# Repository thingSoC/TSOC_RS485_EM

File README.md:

# TSOC_RS485_EM
**TSOC_RS485_EM** is a ATMEGA328 based board with integrated RS485 driver, an Embedded Module for thingSoC.

The **TSOC_RS485_EM** connects any thingSoC or Mikrobus module to an RS485 compatible slave interface,
including a variety of analog sensors, such as Temperature, Wind, Pressure, Air Quality, and much more.
The **TSOC_RS485_EM** can be configured as either a thingSoC master module (female connectors), or a thingSoC slave module (male connectors),
which is implemented as an assembly/build time option.
 
---------------------------------------

[TSOC_RS485_EM](https://github.com/thingSoC/TSOC_RS485_EM/)

* [thingSoC Compliant Module](http://www.thingsoc.com)
* [Mikrobus Compatible Module](http://www.mikroe.com/mikrobus/) 
* [Modbus](http://www.modbus.org/specs.php) Compliant Slave Interface
* [5 Volt](https://en.wikipedia.org/wiki/Modbus) Nominal Power Input with ESD and OV/OC protections
* Supports Analog  Inputs  (ADC) 
* Supports Digital Outputs (GPIO)
* Supports Digital Inputs  (GPIO)
* Supports Remote I2C Interface
* Supports Remote UART Interface
* Supports Remote SPI Interface

## Protocols

* DMX512, RDM512
* Modbus
* Vending Machine Bus

---------------------------------------
## Example Applications

[TSOC_RS485_EM Example Wiring](https://github.com/thingSoC/TSOC_RS485_EM/)

* [Modbus Weather Sensor](http://www.mikroe.com/click/weather/) BOSCH BME280 Temp, Humidity, Air Pressure
* [Modbus Methane Sensor](http://www.mikroe.com/click/methane/) MQ-4 Sensor for Methane (CH4) 
* [Modbus Air Quality Sensor](http://www.mikroe.com/click/air-quality/) MQ-135 Sensor for Harmful Gasses
* [Modbus Lightning Sensor](http://www.mikroe.com/click/thunder/) AS3935 Lighting Strike Detector
* [Modbus Controlled Relay](http://www.mikroe.com/click/relay/) G6D1AASI Power Relay Control Module

---------------------------------------
## 3D Model (Sketchup)

---------------------------------------
## Project Status

* 02/18/2016 : Revision 4.0 Release for PCB fab
* 03/07/2016 : First Prototypes, board bringup is good
* 03/14/2016 : Revision 5.0 Released for PCB
* 04/06/2016 : Revision 6.0 Released for PCB

## Revision 6.0 Notes: ##

* Pinout Changes, D5/D8/D9 added as a second serial choice
* Disconnect jumpers added to all shared pins
* A7 used as AREF calibration input
* A6 used as VCC monitor input
* Both 3.5mm and 2.54mm connector patterns added

---------------------------------------

## Documentation Index <a name="documentation_index"/>

[TSOC_RS485_EM Quick Start Guide](https://github.com/thingSoC/TSOC_RS485_EM/blob/master/TSOC_RS485_EM/docs/QuickStart.md)

[TSOC_RS485_EM User Guide](https://github.com/thingSoC/TSOC_RS485_EM/blob/master/TSOC_RS485_EM/docs/UserGuide.md)

[TSOC_RS485_EM Theory of Operation](https://github.com/thingSoC/TSOC_RS485_EM/blob/master/TSOC_RS485_EM/docs/TheoryOfOperation.md)

[thingSoC Organization Website](http://thingSoC.github.io)

[thingSoC FAQ - Frequently Asked Questions](http://thingsoc.github.io/support/faq.html)

---------------------------------------

[  
*thingSoC*](http://thingsoc.github.io)

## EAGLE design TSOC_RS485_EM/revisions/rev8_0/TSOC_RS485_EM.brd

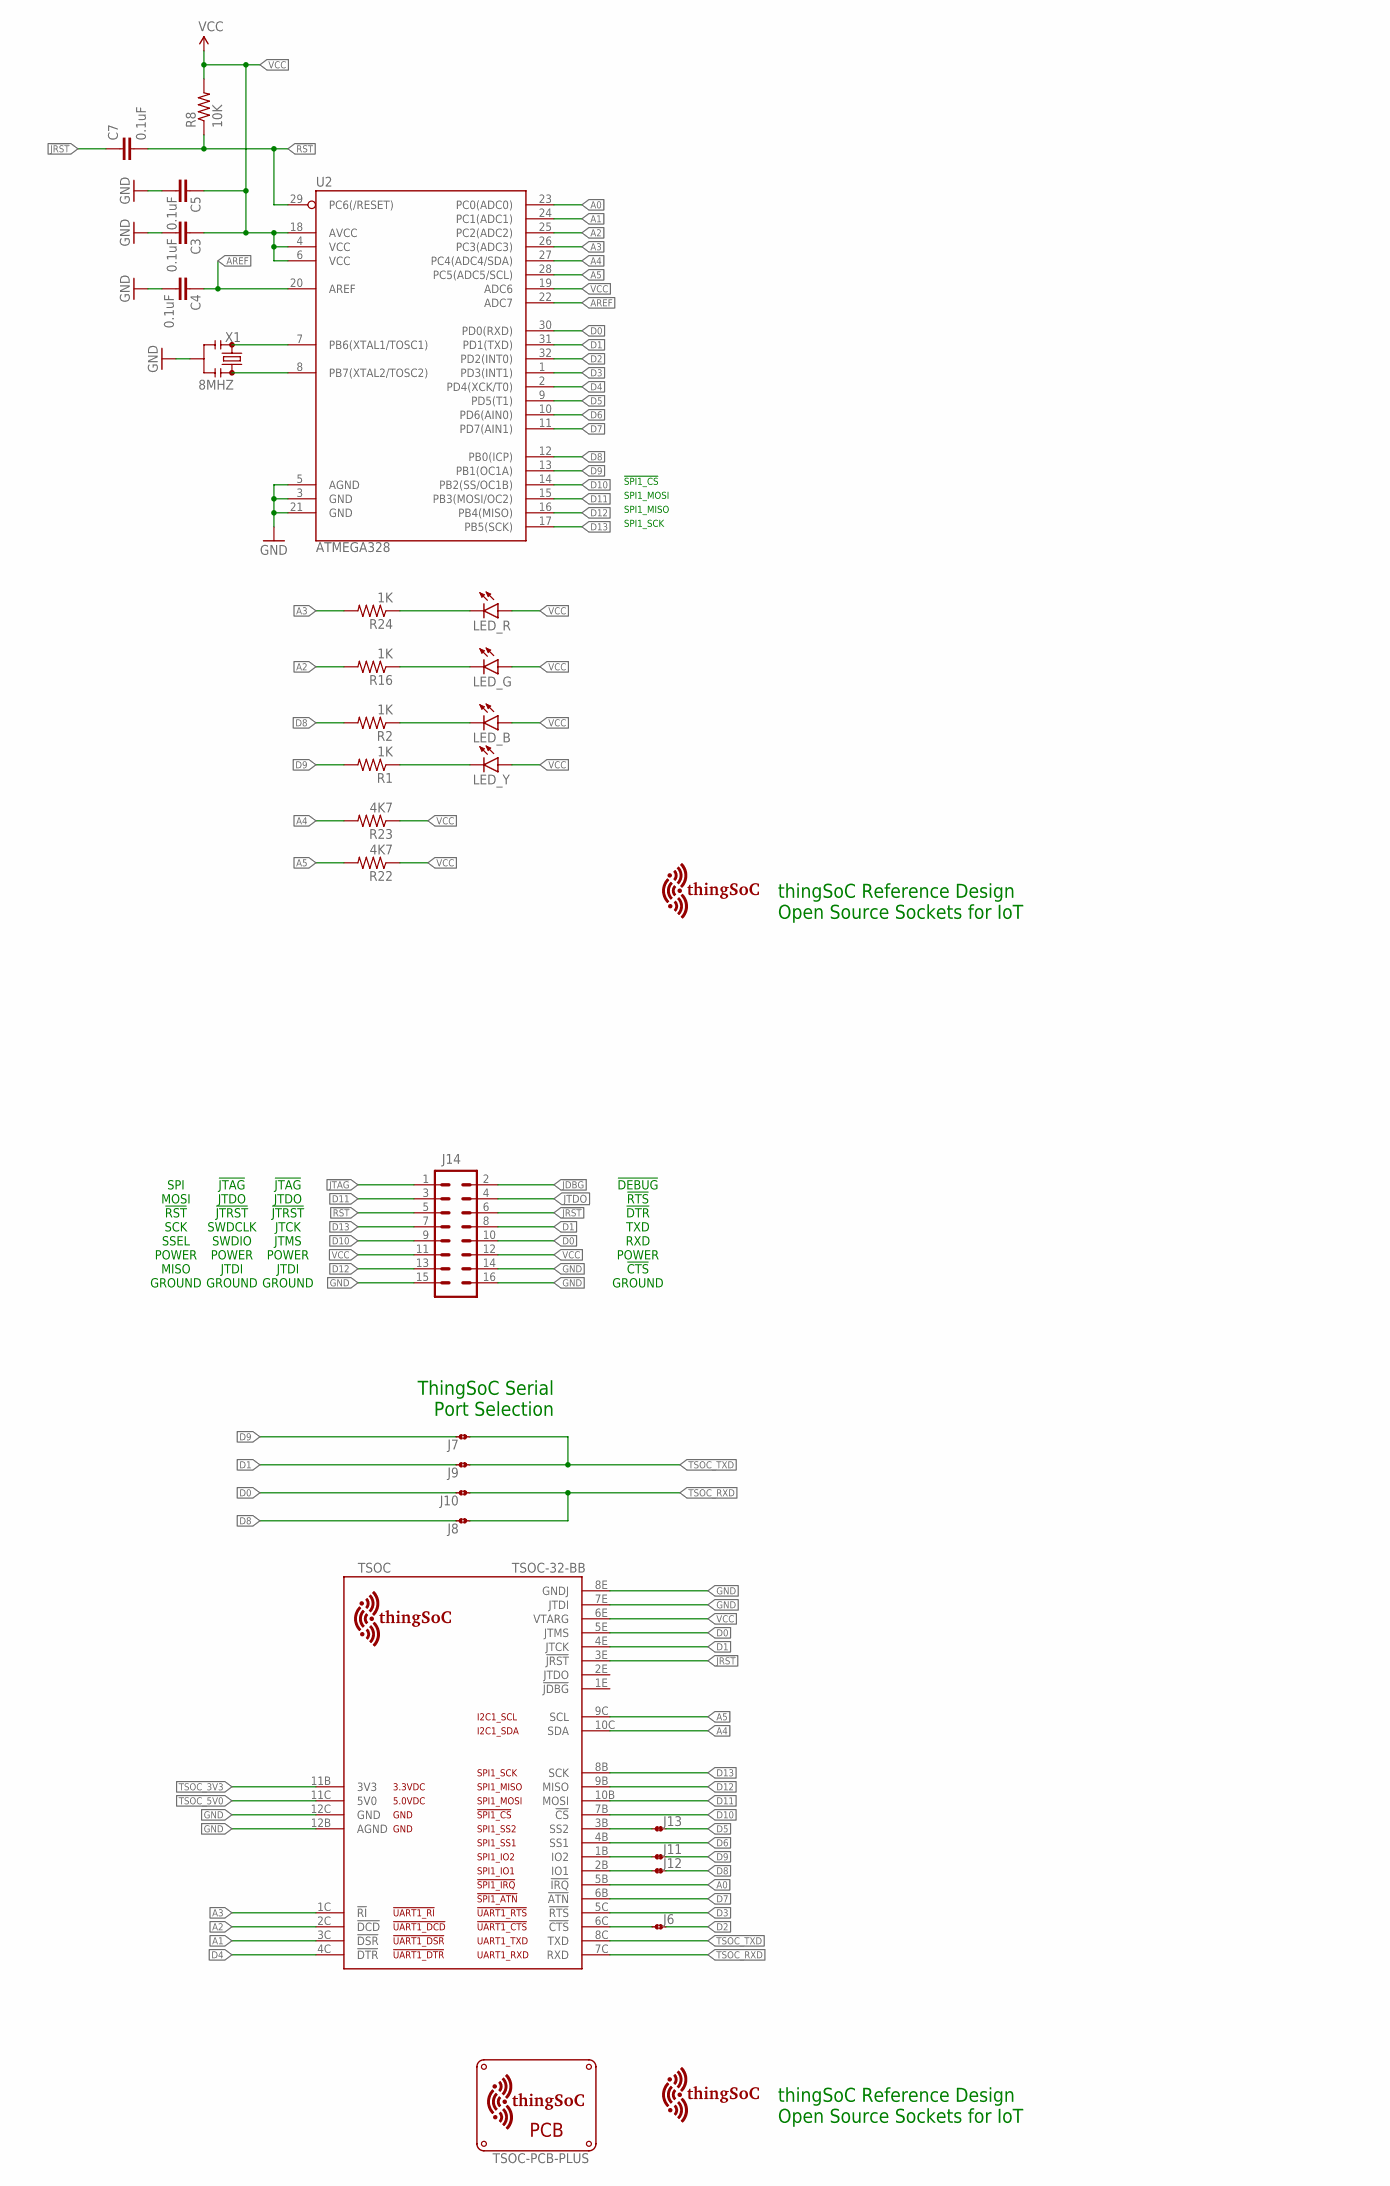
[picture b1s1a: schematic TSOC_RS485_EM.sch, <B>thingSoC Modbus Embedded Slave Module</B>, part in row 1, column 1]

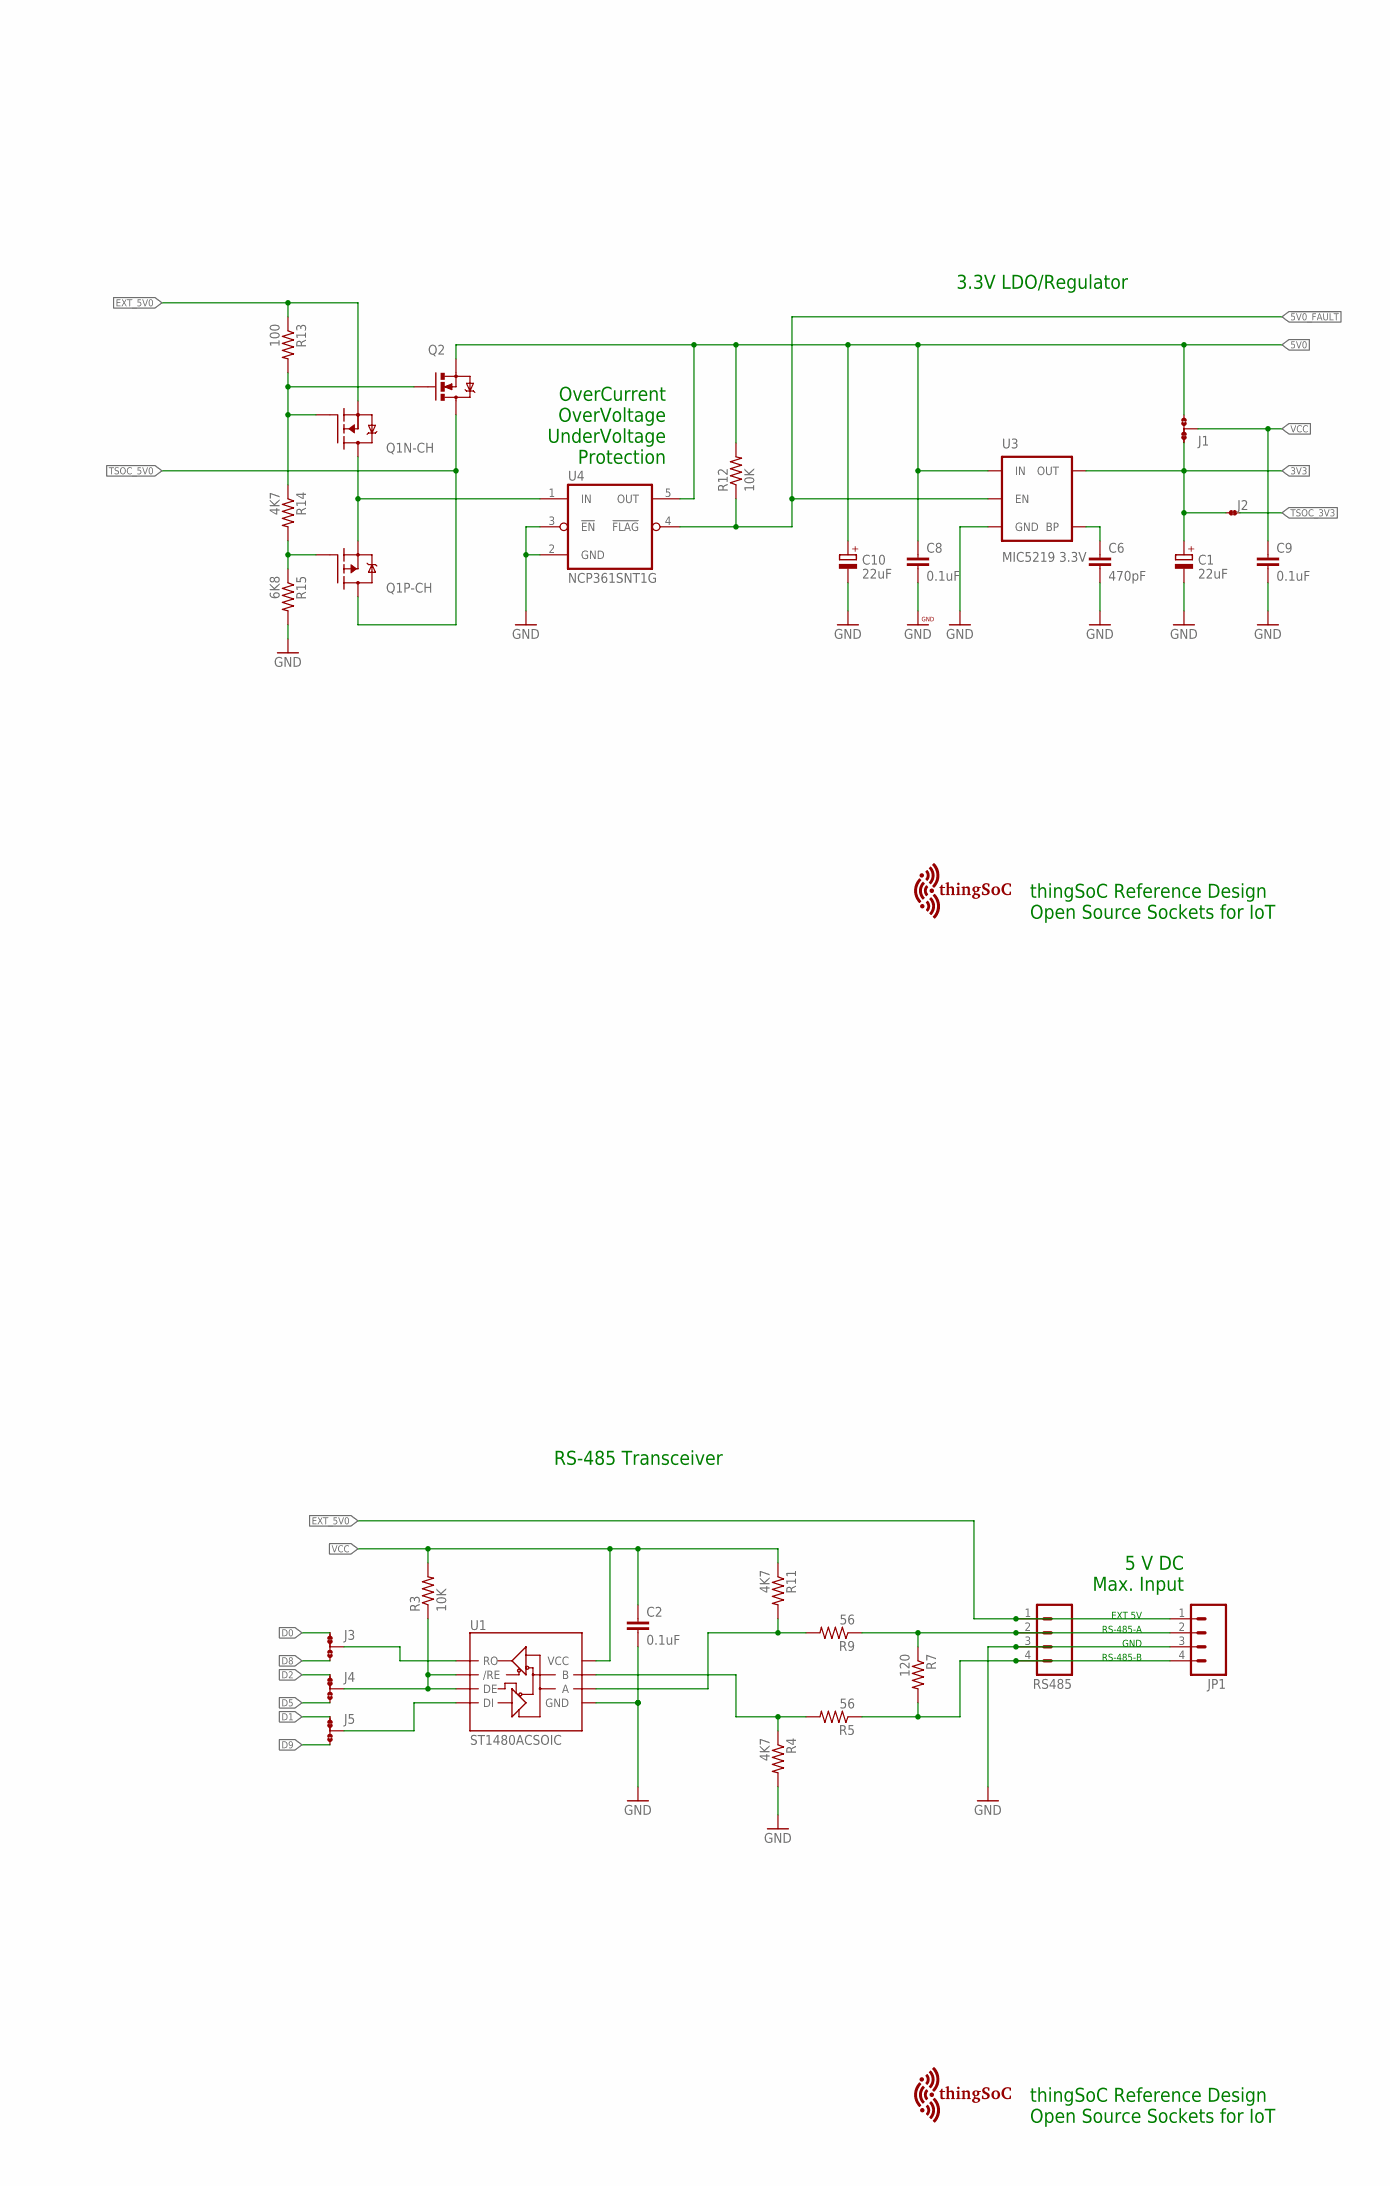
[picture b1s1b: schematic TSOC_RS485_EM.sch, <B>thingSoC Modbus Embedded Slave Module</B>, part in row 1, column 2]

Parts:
C1, C10: 22uF; SMC_B
C2, C3, C4, C5, C7, C8, C9: 0.1uF; EIA-0402
C6: 470pF; EIA-0402
J1, J3, J4, J5: JMP-3-1_2
J2, J11, J12, J13: JMP-2-NC
J6, J7, J8, J9, J10: JMP-2-NO
J14: M08X2; 2X8
JP1: M04PTH; 1X04
LED_B: LED0603; LED-0603
LED_G: LED0603; LED-0603
LED_R: LED0603; LED-0603
LED_Y: LED0603; LED-0603
Q1: FDC6420C; SOT95P280X110-6N
Q2: MOSFET-NCHANNELAO3404A; SOT23-3
R1, R2, R16, R24: 1K; EIA-0402-MIN
R3, R8, R12: 10K; EIA-0402-MIN
R4, R11, R14, R22, R23: 4K7; EIA-0402-MIN
R5, R9: 56; EIA-0402-MIN
R7: 120; EIA-0402-MIN
R13: 100; EIA-0402-MIN
R15: 6K8; EIA-0402-MIN
RS485: M04SCREW; SCREWTERMINAL-3.5MM-4
TSOC: TSOC-32-BB; TSOC-BB-S32
U1: ST1480ACSOIC; SO08
U2: ATMEGA328; TQFP32-08
U3: MIC5219 3.3V; SOT23-5
U4: NCP361SNT1G; SOP95P275X110-5N
U$3: TSOC-PCB-PLUS; TSOC-BB-BRD-PLUS
U$5, U$6, U$7, U$8: TSOC-LOGO-SMALL; TSOC-LOGO-SML
X1: 8MHZ; RESONATOR-SMD

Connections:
3V3: C1.+, J1.1, J2.1, U3.5 (OUT)
5V0: C8.1, C10.+, J1.3, Q2.2 (S), R12.2, U3.1 (IN), U4.5 (OUT)
!5V0_FAULT: R12.1, U3.3 (EN), U4.4 (!FLAG)
!JDBG: J14.2
!JRST: C7.1, J14.6, TSOC.3E (!JRST)
!JTAG: J14.1
!RST: C7.2, J14.5, R8.1, U2.29 (PC6(/RESET))
A: R9.2, R11.2, U1.6 (A)
A0: TSOC.5B (!IRQ), U2.23 (PC0(ADC0))
A1: TSOC.3C (!DSR), U2.24 (PC1(ADC1))
A2: R16.2, TSOC.2C (!DCD), U2.25 (PC2(ADC2))
A3: R24.2, TSOC.1C (!RI), U2.26 (PC3(ADC3))
A4: R23.2, TSOC.10C (SDA), U2.27 (PC4(ADC4/SDA))
A5: R22.2, TSOC.9C (SCL), U2.28 (PC5(ADC5/SCL))
AO: JP1.2, R7.1, R9.1, RS485.2
AREF: C4.2, U2.20 (AREF), U2.22 (ADC7)
B: R4.1, R5.2, U1.7 (B)
BO: JP1.4, R5.1, R7.2, RS485.4
BYPASS1: C6.1, U3.4 (BP)
D0: J3.1, J10.2, J14.10, TSOC.5E (JTMS), U2.30 (PD0(RXD))
D1: J5.1, J9.2, J14.8, TSOC.4E (JTCK), U2.31 (PD1(TXD))
D2: J4.1, J6.2, U2.32 (PD2(INT0))
D3: TSOC.5C (!RTS), U2.1 (PD3(INT1))
D4: TSOC.4C (!DTR), U2.2 (PD4(XCK/T0))
D5: J4.3, J13.2, U2.9 (PD5(T1))
D6: TSOC.4B (SS1), U2.10 (PD6(AIN0))
D7: TSOC.6B (!ATN), U2.11 (PD7(AIN1))
D8: J3.3, J8.2, J12.2, R2.2, U2.12 (PB0(ICP))
D9: J5.3, J7.2, J11.2, R1.2, U2.13 (PB1(OC1A))
D10: J14.9, TSOC.7B (!CS), U2.14 (PB2(SS/OC1B))
D11: J14.3, TSOC.10B (MOSI), U2.15 (PB3(MOSI/OC2))
D12: J14.13, TSOC.9B (MISO), U2.16 (PB4(MISO))
D13: J14.7, TSOC.8B (SCK), U2.17 (PB5(SCK))
DE: J4.2, R3.1, U1.2 (/RE), U1.3 (DE)
DI: J5.2, U1.4 (DI)
EXT_5V0: JP1.1, Q1.5 (S), R13.1, RS485.1
GND: C1.-, C2.2, C3.1, C4.1, C5.1, C6.2, C8.2, C9.2, C10.-, J14.14, J14.15, J14.16, JP1.3, R4.2, R15.2, RS485.3, TSOC.7E (JTDI), TSOC.8E (GNDJ), TSOC.12B (AGND), TSOC.12C (GND), U1.5 (GND), U2.3 (GND), U2.5 (AGND), U2.21 (GND), U3.2 (GND), U4.2 (GND), U4.3 (!EN), X1.2
JTDO: J14.4
LEDB: LED_B.C, R2.1
LEDG: LED_G.C, R16.1
LEDR: LED_R.C, R24.1
LEDY: LED_Y.C, R1.1
unnamed: J13.1, TSOC.3B (SS2)
NGATE: Q1.1 (G), Q2.1 (G), R13.2, R14.1
PGATE: Q1.3 (G), R14.2, R15.1
RXD: J3.2, U1.1 (RO)
TSOC_3V3: J2.2, TSOC.11B (3V3)
TSOC_5V0: Q1.4 (D), Q2.3 (D), TSOC.11C (5V0)
TSOC_CTS: J6.1, TSOC.6C (!CTS)
TSOC_D8: J12.1, TSOC.2B (IO1)
TSOC_D9: J11.1, TSOC.1B (IO2)
TSOC_RXD: J8.1, J10.1, TSOC.7C (RXD)
TSOC_TXD: J7.1, J9.1, TSOC.8C (TXD)
VCC: C2.1, C3.2, C5.2, C9.1, J1.2, J14.11, J14.12, LED_B.A, LED_G.A, LED_R.A, LED_Y.A, R3.2, R8.2, R11.1, R22.1, R23.1, TSOC.6E (VTARG), U1.8 (VCC), U2.4 (VCC), U2.6 (VCC), U2.18 (AVCC), U2.19 (ADC6)
VIN: Q1.2 (S), Q1.6 (D), U4.1 (IN)
XIN: U2.7 (PB6(XTAL1/TOSC1)), X1.3
XOUT: U2.8 (PB7(XTAL2/TOSC2)), X1.1

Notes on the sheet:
SPI1_SCK
SPI1_MISO
SPI1_MOSI
!SPI1_CS
5 V DC Max. Input
OverCurrent OverVoltage UnderVoltage Protection
3.3V LDO/Regulator
RS-485 Transceiver
EXT 5V
GND
RS-485-A
RS-485-B
ThingSoC Serial Port Selection
thingSoC Reference Design Open Source Sockets for IoT
!DEBUG
!RTS
!CTS
!DTR
TXD
RXD
POWER
GROUND
JTDI
JTDO
!JTRST
JTCK
JTMS
!JTAG
SWDCLK
SWDIO
SCK
SSEL
SPI
MOSI
!RST
MISO

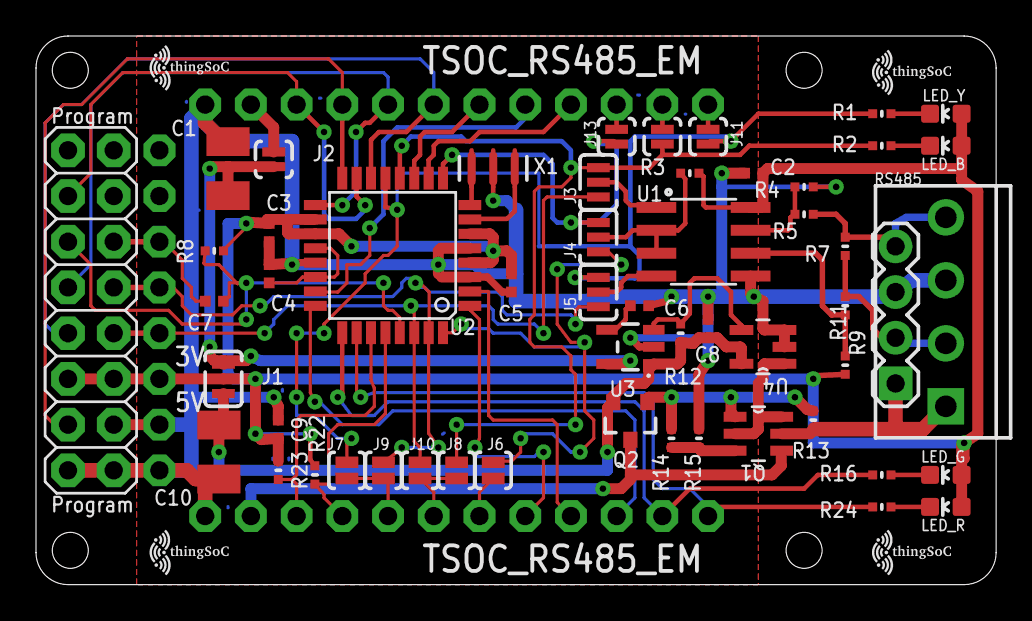
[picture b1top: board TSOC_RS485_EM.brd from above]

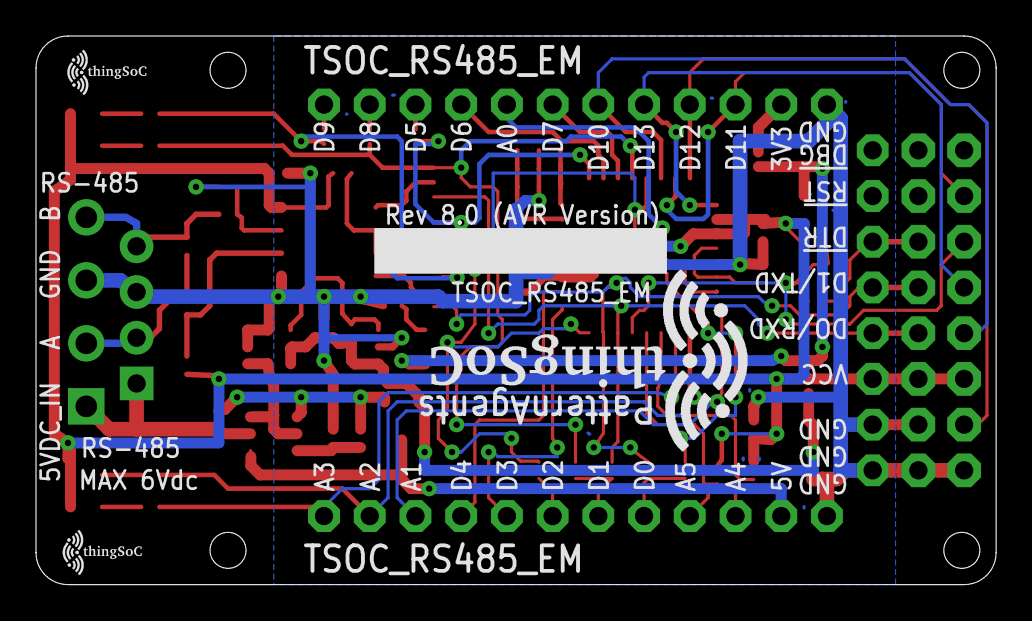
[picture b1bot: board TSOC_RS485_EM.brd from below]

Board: 2 copper layers, 53.3 x 30.5 mm, 63 parts (3 on the bottom side), 54 nets.

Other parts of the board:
U$1, U$4: TSOC-LOGO-SMALL; TSOC-LOGO-SML
U$100: TSOC-LOGO-LRG

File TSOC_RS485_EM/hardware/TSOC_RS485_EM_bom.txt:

Partlist exported from /home/moxon/github/TSOC_RS485_EM/TSOC_RS485_EM/TSOC_RS485_EM.sch at 4/6/16 2:10 PM

Qty Value                  Device                 Package               Parts                      Description                                            
5                          JMP-2-NO               JMP-2-NO              J6, J7, J8, J9, J10        Two Terminal Jumper - Normally Open                    
4                          LED0603                LED-0603              LED_B, LED_G, LED_R, LED_Y LEDs                                                   
1                          M04PTH                 1X04                  JP1                        Header 4                                               
1                          M04SCREW               SCREWTERMINAL-3.5MM-4 RS485                      Header 4                                               
7   0.1uF                  CAP0402-CAP            0402-CAP              C2, C3, C4, C5, C7, C8, C9 Capacitor                                              
1   100                    RESISTOR0402           0402-RES              R13                        Resistor                                               
3   10K                    RESISTOR0402           0402-RES              R3, R8, R12                Resistor                                               
1   120                    RESISTOR0402           0402-RES              R7                         Resistor                                               
4   1K                     RESISTOR0402           0402-RES              R1, R2, R16, R24           Resistor                                               
2   22uF                   CPOL-EUSMCB            SMC_B                 C1, C10                    POLARIZED CAPACITOR, European symbol                   
1   470pF                  CAP0402-CAP            0402-CAP              C6                         Capacitor                                              
5   4K7                    RESISTOR0402           0402-RES              R4, R11, R14, R22, R23     Resistor                                               
2   56                     RESISTOR0402           0402-RES              R5, R9                     Resistor                                               
1   6K8                    RESISTOR0402           0402-RES              R15                        Resistor                                               
1   8MHZ                   RESONATOR8MHZ          RESONATOR-SMD         X1                         Resonator                                              
1   ATMEGA328              ATMEGA168              TQFP32-08             U2                                                                                
2   DNP                    RESISTOR0402           0402-RES              R6, R10                    Resistor                                               
1   FDC6420C               FDC6420C               SOT95P280X110-6N      Q1                         N and P Channel Power Trench MOSFETs                   
4   JMP-2-NC               JMP-2-NC               JMP-2-NC              J2, J11, J12, J13          Two Terminal Jumper - Normally Closed                  
4   JMP-3-1_2              JMP-3-1_2              JMP-3-1_2             J1, J3, J4, J5             Three Terminal Jumper - 1 & 2 Connected                
1   MIC5219 3.3V           V_REG_MIC52193.3V      SOT23-5               U3                         V_REG MIC5219                                          
1   MOSFET-NCHANNELAO3404A MOSFET-NCHANNELAO3404A SOT23-3               Q2                         Common NMOSFET Parts                                   
1   NCP361SNT1G            NCP361SNT1G            SOP95P275X110-5N      U4                         USB Positive Overvoltage Protection Controller         
1   ST1480ACSOIC           ST1480ACSOIC           SO08                  U1                         ST Microelectronics ST1480AC RS-485/RS-422 Transceiver 
1   TSOC-32-BB             TSOC-32-BB             TSOC-BB-S32           TSOC                       thingSoC Thirty-Two (32) Pin Socket                    
1   TSOC-PCB-EM-45         TSOC-PCB-EM-45         TSOC-EM-BB-45MM       U$1                        thingSoC PCB Outlines

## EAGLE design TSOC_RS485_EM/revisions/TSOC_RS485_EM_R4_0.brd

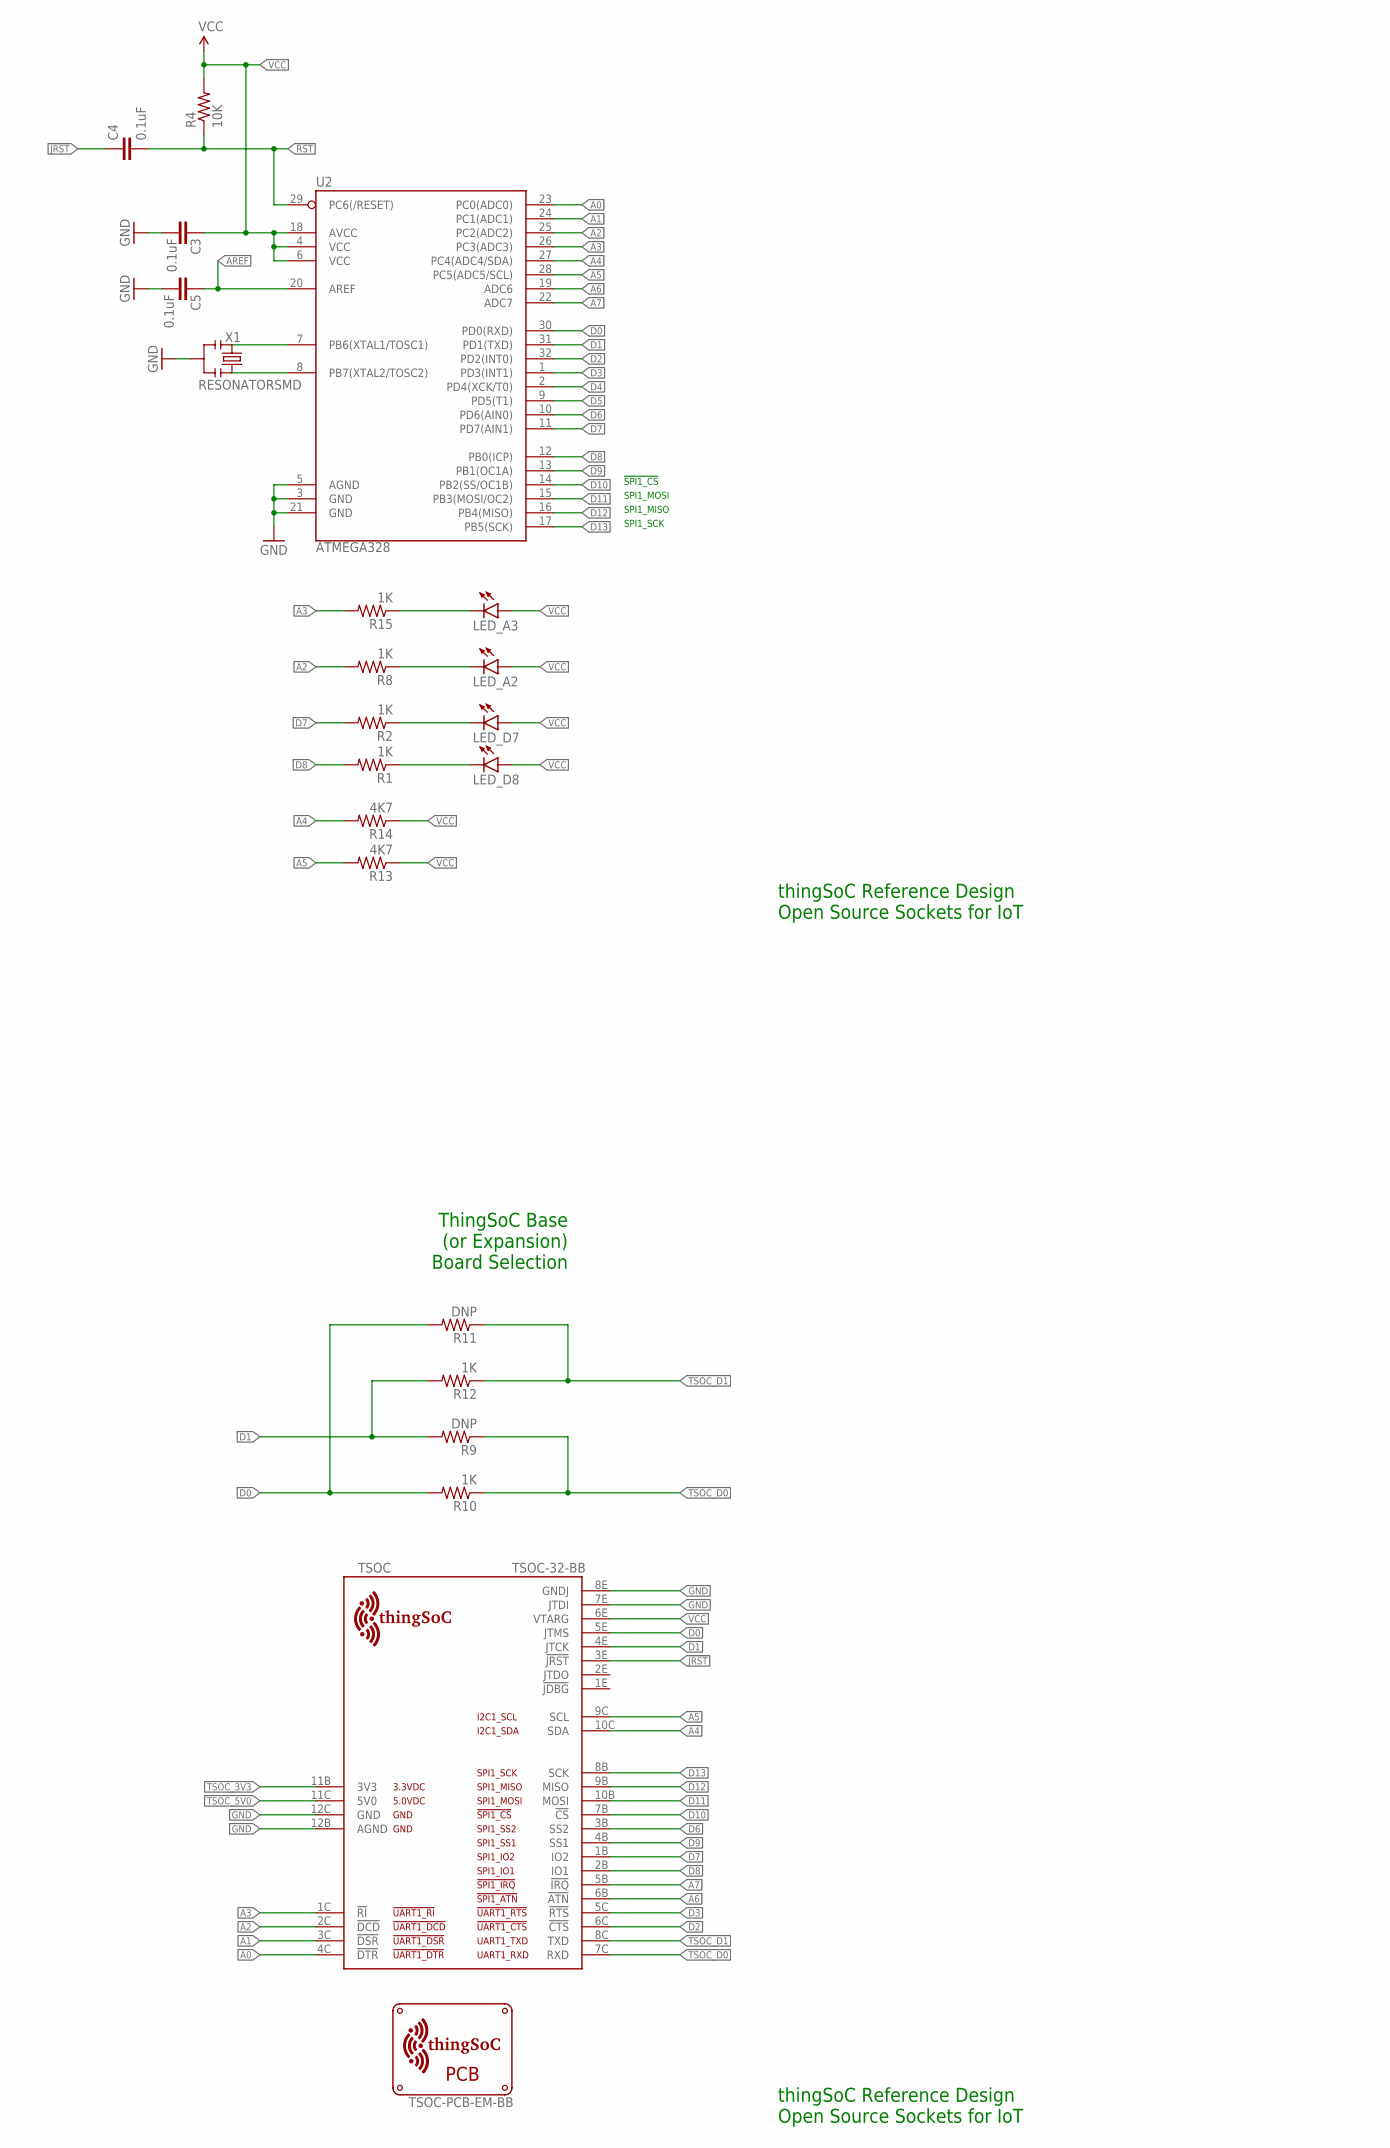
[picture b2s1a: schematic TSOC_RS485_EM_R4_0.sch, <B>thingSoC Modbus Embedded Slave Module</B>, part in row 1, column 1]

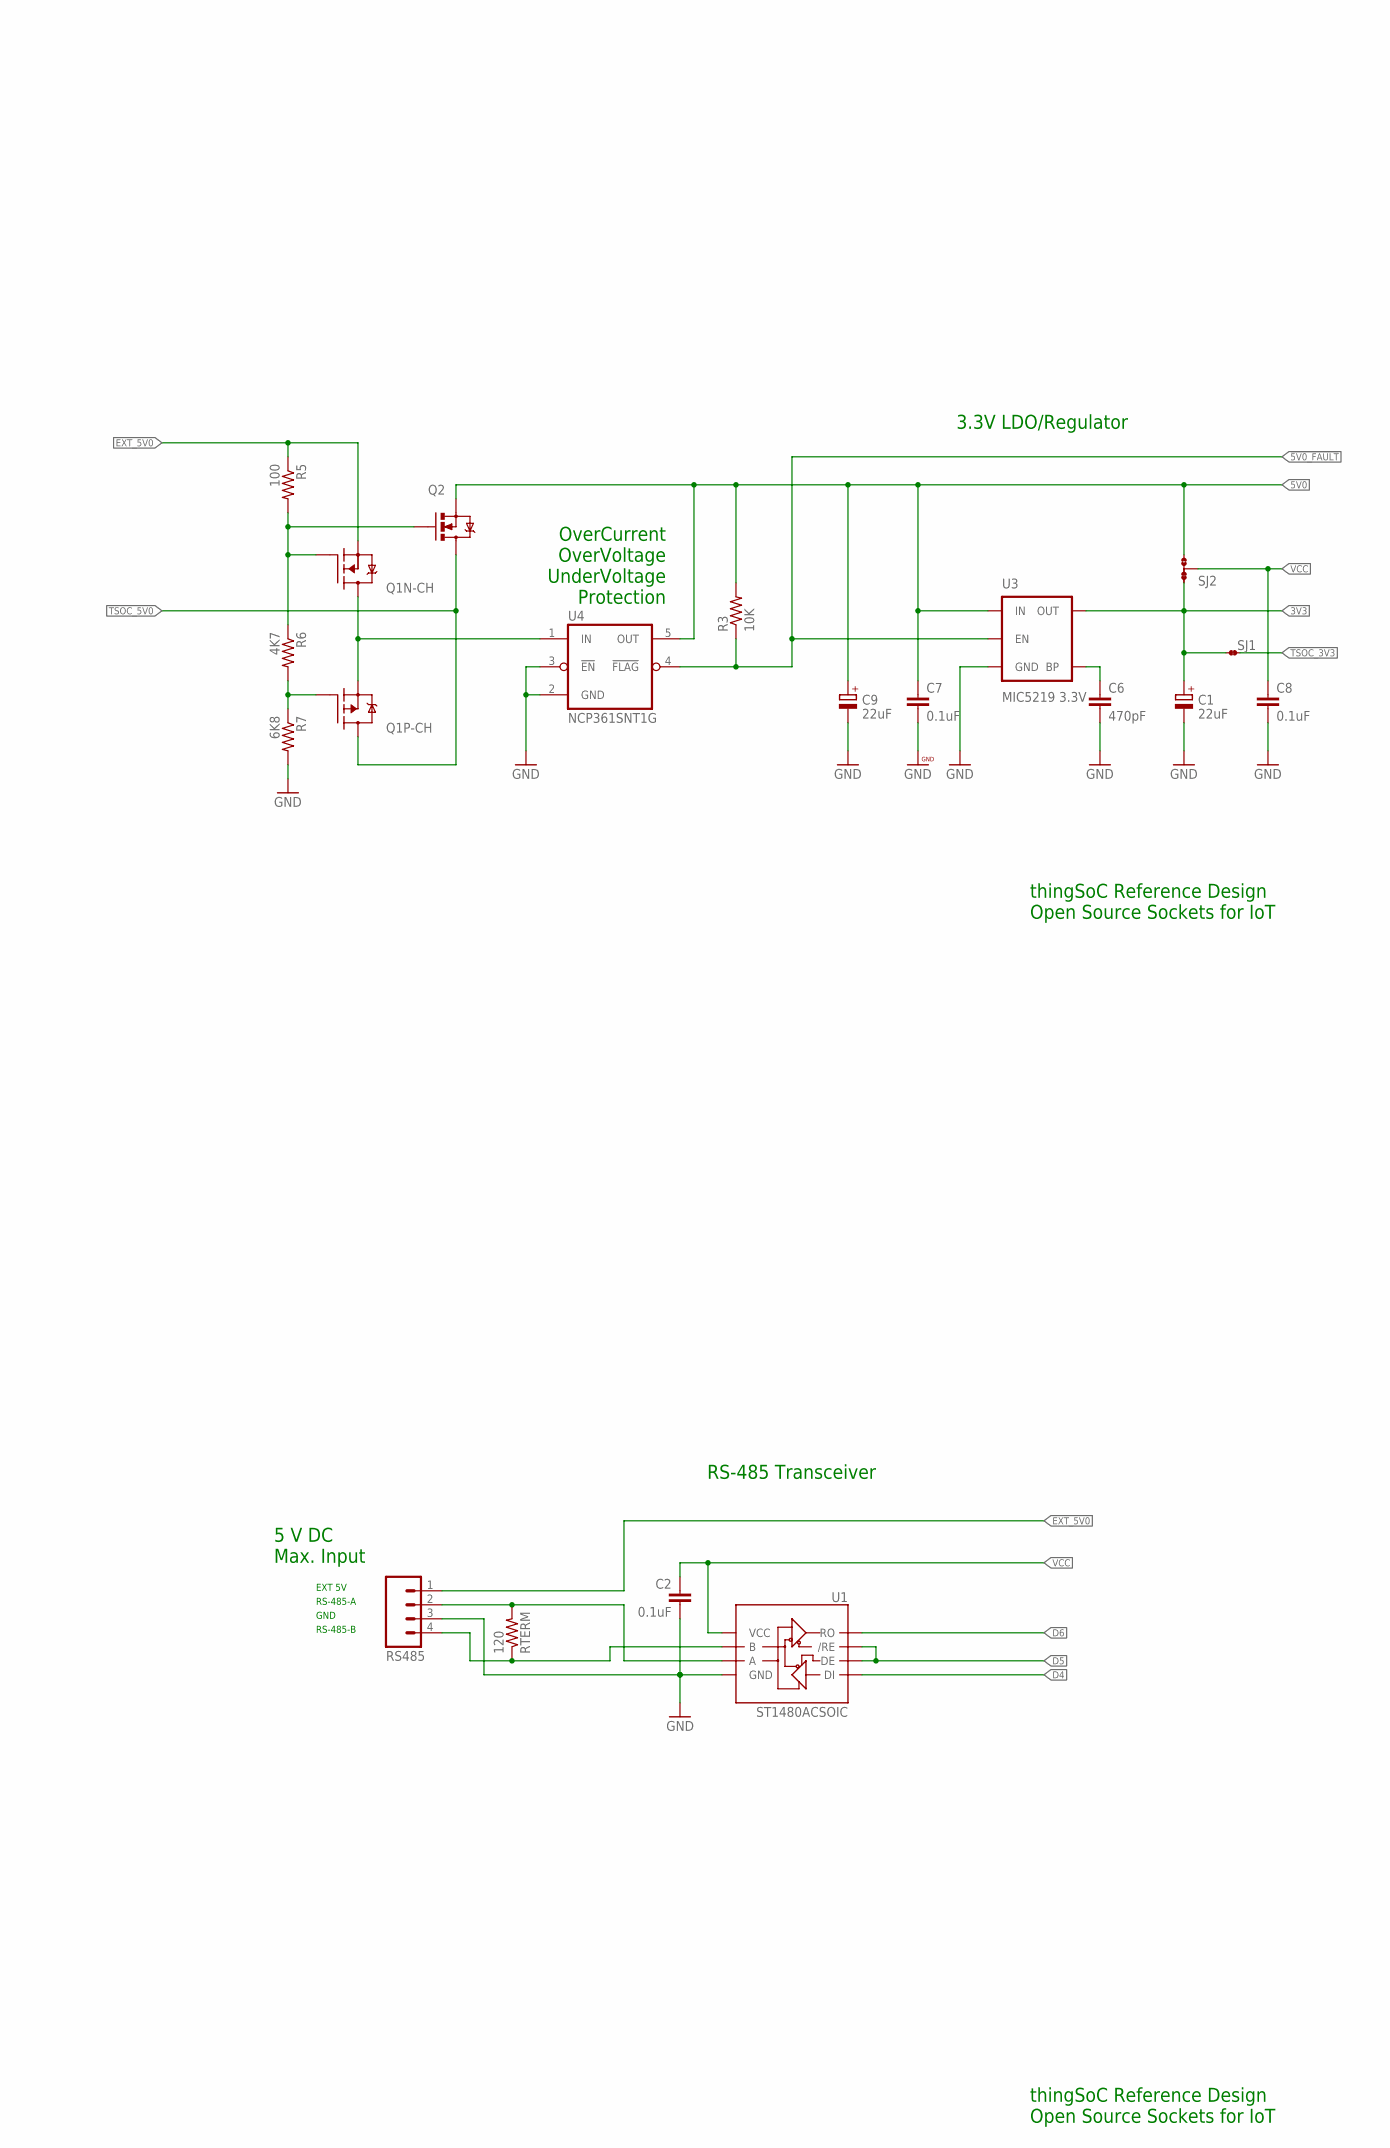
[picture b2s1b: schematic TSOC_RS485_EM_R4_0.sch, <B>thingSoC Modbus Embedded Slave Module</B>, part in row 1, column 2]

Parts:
C1, C9: 22uF; SMC_B
C2, C3, C4, C5, C7, C8: 0.1uF; 0402-CAP
C6: 470pF; 0402-CAP
LED_A2, LED_A3: LED0603; LED-0603
LED_D7, LED_D8: LED0603; LED-0603
Q1: FDC6420C; SOT95P280X110-6N
Q2: MOSFET-NCHANNELAO3404A; SOT23-3
R1, R2, R8, R10, R12, R15: 1K; 0402-RES
R3, R4: 10K; 0402-RES
R5: 100; 0402-RES
R6, R13, R14: 4K7; 0402-RES
R7: 6K8; 0402-RES
R9, R11: DNP; 0402-RES
RS485: M04SCREW; SCREWTERMINAL-3.5MM-4
RTERM: 120; 0402-RES
SJ1: JMP-2-NC
SJ2: JMP-3-1_2
TSOC: TSOC-32-BB; TSOC-BB-S32
U1: ST1480ACSOIC; SO08
U2: ATMEGA328; TQFP32-08
U3: MIC5219 3.3V; SOT23-5
U4: NCP361SNT1G; SOP95P275X110-5N
U$1: TSOC-PCB-EM-BB; TSOC-EM-BB
X1: RESONATORSMD; RESONATOR-SMD

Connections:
3V3: C1.+, SJ1.1, SJ2.1, U3.5 (OUT)
5V0: C7.1, C9.+, Q2.2 (S), R3.2, SJ2.3, U3.1 (IN), U4.5 (OUT)
!5V0_FAULT: R3.1, U3.3 (EN), U4.4 (!FLAG)
!JRST: C4.1, TSOC.3E (!JRST)
!RST: C4.2, R4.1, U2.29 (PC6(/RESET))
A: RS485.4, RTERM.1, U1.7 (B)
A0: TSOC.4C (!DTR), U2.23 (PC0(ADC0))
A1: TSOC.3C (!DSR), U2.24 (PC1(ADC1))
A2: R8.2, TSOC.2C (!DCD), U2.25 (PC2(ADC2))
A3: R15.2, TSOC.1C (!RI), U2.26 (PC3(ADC3))
A4: R14.2, TSOC.10C (SDA), U2.27 (PC4(ADC4/SDA))
A5: R13.2, TSOC.9C (SCL), U2.28 (PC5(ADC5/SCL))
A6: TSOC.6B (!ATN), U2.19 (ADC6)
A7: TSOC.5B (!IRQ), U2.22 (ADC7)
AREF: C5.2, U2.20 (AREF)
B: RS485.2, RTERM.2, U1.6 (A)
BYPASS1: C6.1, U3.4 (BP)
D0: R10.2, R11.2, TSOC.5E (JTMS), U2.30 (PD0(RXD))
D1: R9.2, R12.2, TSOC.4E (JTCK), U2.31 (PD1(TXD))
D2: TSOC.6C (!CTS), U2.32 (PD2(INT0))
D3: TSOC.5C (!RTS), U2.1 (PD3(INT1))
D4: U1.4 (DI), U2.2 (PD4(XCK/T0))
D5: U1.2 (/RE), U1.3 (DE), U2.9 (PD5(T1))
D6: TSOC.3B (SS2), U1.1 (RO), U2.10 (PD6(AIN0))
D7: R2.2, TSOC.1B (IO2), U2.11 (PD7(AIN1))
D8: R1.2, TSOC.2B (IO1), U2.12 (PB0(ICP))
D9: TSOC.4B (SS1), U2.13 (PB1(OC1A))
D10: TSOC.7B (!CS), U2.14 (PB2(SS/OC1B))
D11: TSOC.10B (MOSI), U2.15 (PB3(MOSI/OC2))
D12: TSOC.9B (MISO), U2.16 (PB4(MISO))
D13: TSOC.8B (SCK), U2.17 (PB5(SCK))
EXT_5V0: Q1.5 (S), R5.1, RS485.1
GND: C1.-, C2.2, C3.1, C5.1, C6.2, C7.2, C8.2, C9.-, R7.2, RS485.3, TSOC.7E (JTDI), TSOC.8E (GNDJ), TSOC.12B (AGND), TSOC.12C (GND), U1.5 (GND), U2.3 (GND), U2.5 (AGND), U2.21 (GND), U3.2 (GND), U4.2 (GND), U4.3 (!EN), X1.2
LED_A2: LED_A2.C, R8.1
unnamed: LED_D7.C, R2.1
unnamed: LED_A3.C, R15.1
unnamed: LED_D8.C, R1.1
NGATE: Q1.1 (G), Q2.1 (G), R5.2, R6.1
PGATE: Q1.3 (G), R6.2, R7.1
TSOC_3V3: SJ1.2, TSOC.11B (3V3)
TSOC_5V0: Q1.4 (D), Q2.3 (D), TSOC.11C (5V0)
TSOC_D0: R9.1, R10.1, TSOC.7C (RXD)
TSOC_D1: R11.1, R12.1, TSOC.8C (TXD)
VCC: C2.1, C3.2, C8.1, LED_A2.A, LED_A3.A, LED_D7.A, LED_D8.A, R4.2, R13.1, R14.1, SJ2.2, TSOC.6E (VTARG), U1.8 (VCC), U2.4 (VCC), U2.6 (VCC), U2.18 (AVCC)
VIN: Q1.2 (S), Q1.6 (D), U4.1 (IN)
XIN: U2.7 (PB6(XTAL1/TOSC1)), X1.3
XOUT: U2.8 (PB7(XTAL2/TOSC2)), X1.1

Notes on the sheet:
SPI1_SCK
SPI1_MISO
SPI1_MOSI
!SPI1_CS
5 V DC Max. Input
OverCurrent OverVoltage UnderVoltage Protection
3.3V LDO/Regulator
RS-485 Transceiver
EXT 5V
GND
RS-485-A
RS-485-B
ThingSoC Base (or Expansion) Board Selection
thingSoC Reference Design Open Source Sockets for IoT

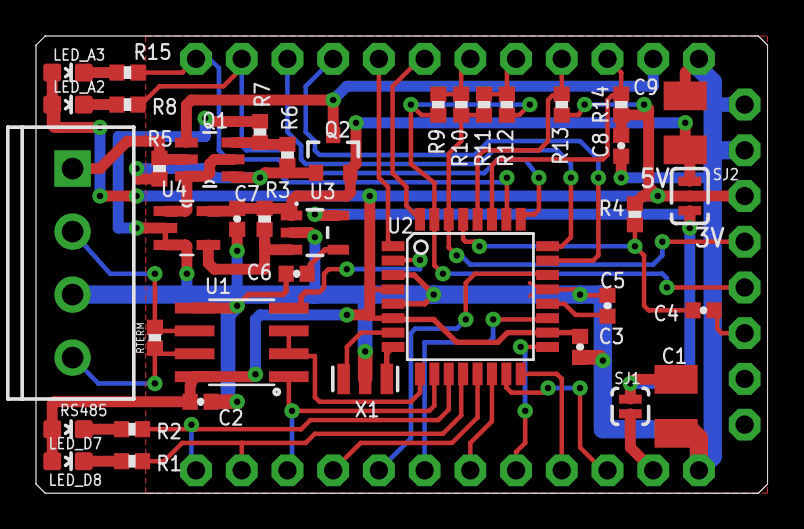
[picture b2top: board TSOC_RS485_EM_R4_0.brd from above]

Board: 2 copper layers, 40.6 x 25.4 mm, 42 parts (1 on the bottom side), 47 nets.

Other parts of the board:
U$100: TSOC-LOGO-LRG

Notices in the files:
parts and their libraries:
PatternAgents-Beautify: License : http://creativecommons.org/licenses/by-sa/3.0
(Creative Commons 3.0)
thingSoC: License : http://creativecommons.org/licenses/by-sa/4.0
(Creative Commons 4.0)
